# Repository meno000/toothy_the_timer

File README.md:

# toothy_the_timer
A little PCB project that helps kids brush teeth for the proper amount of time.

It uses the Atmet Attiny85 along with some shift registers and various LEDs, etc.

Schematics were created in KiCad. Gerbers are available if you'd like to send the board out to a fab house.

Note that this repository does not have a bootloader in it. You'll have to find/roll your own. This is mainly to avoid any issues with USB VID/PID numbers.

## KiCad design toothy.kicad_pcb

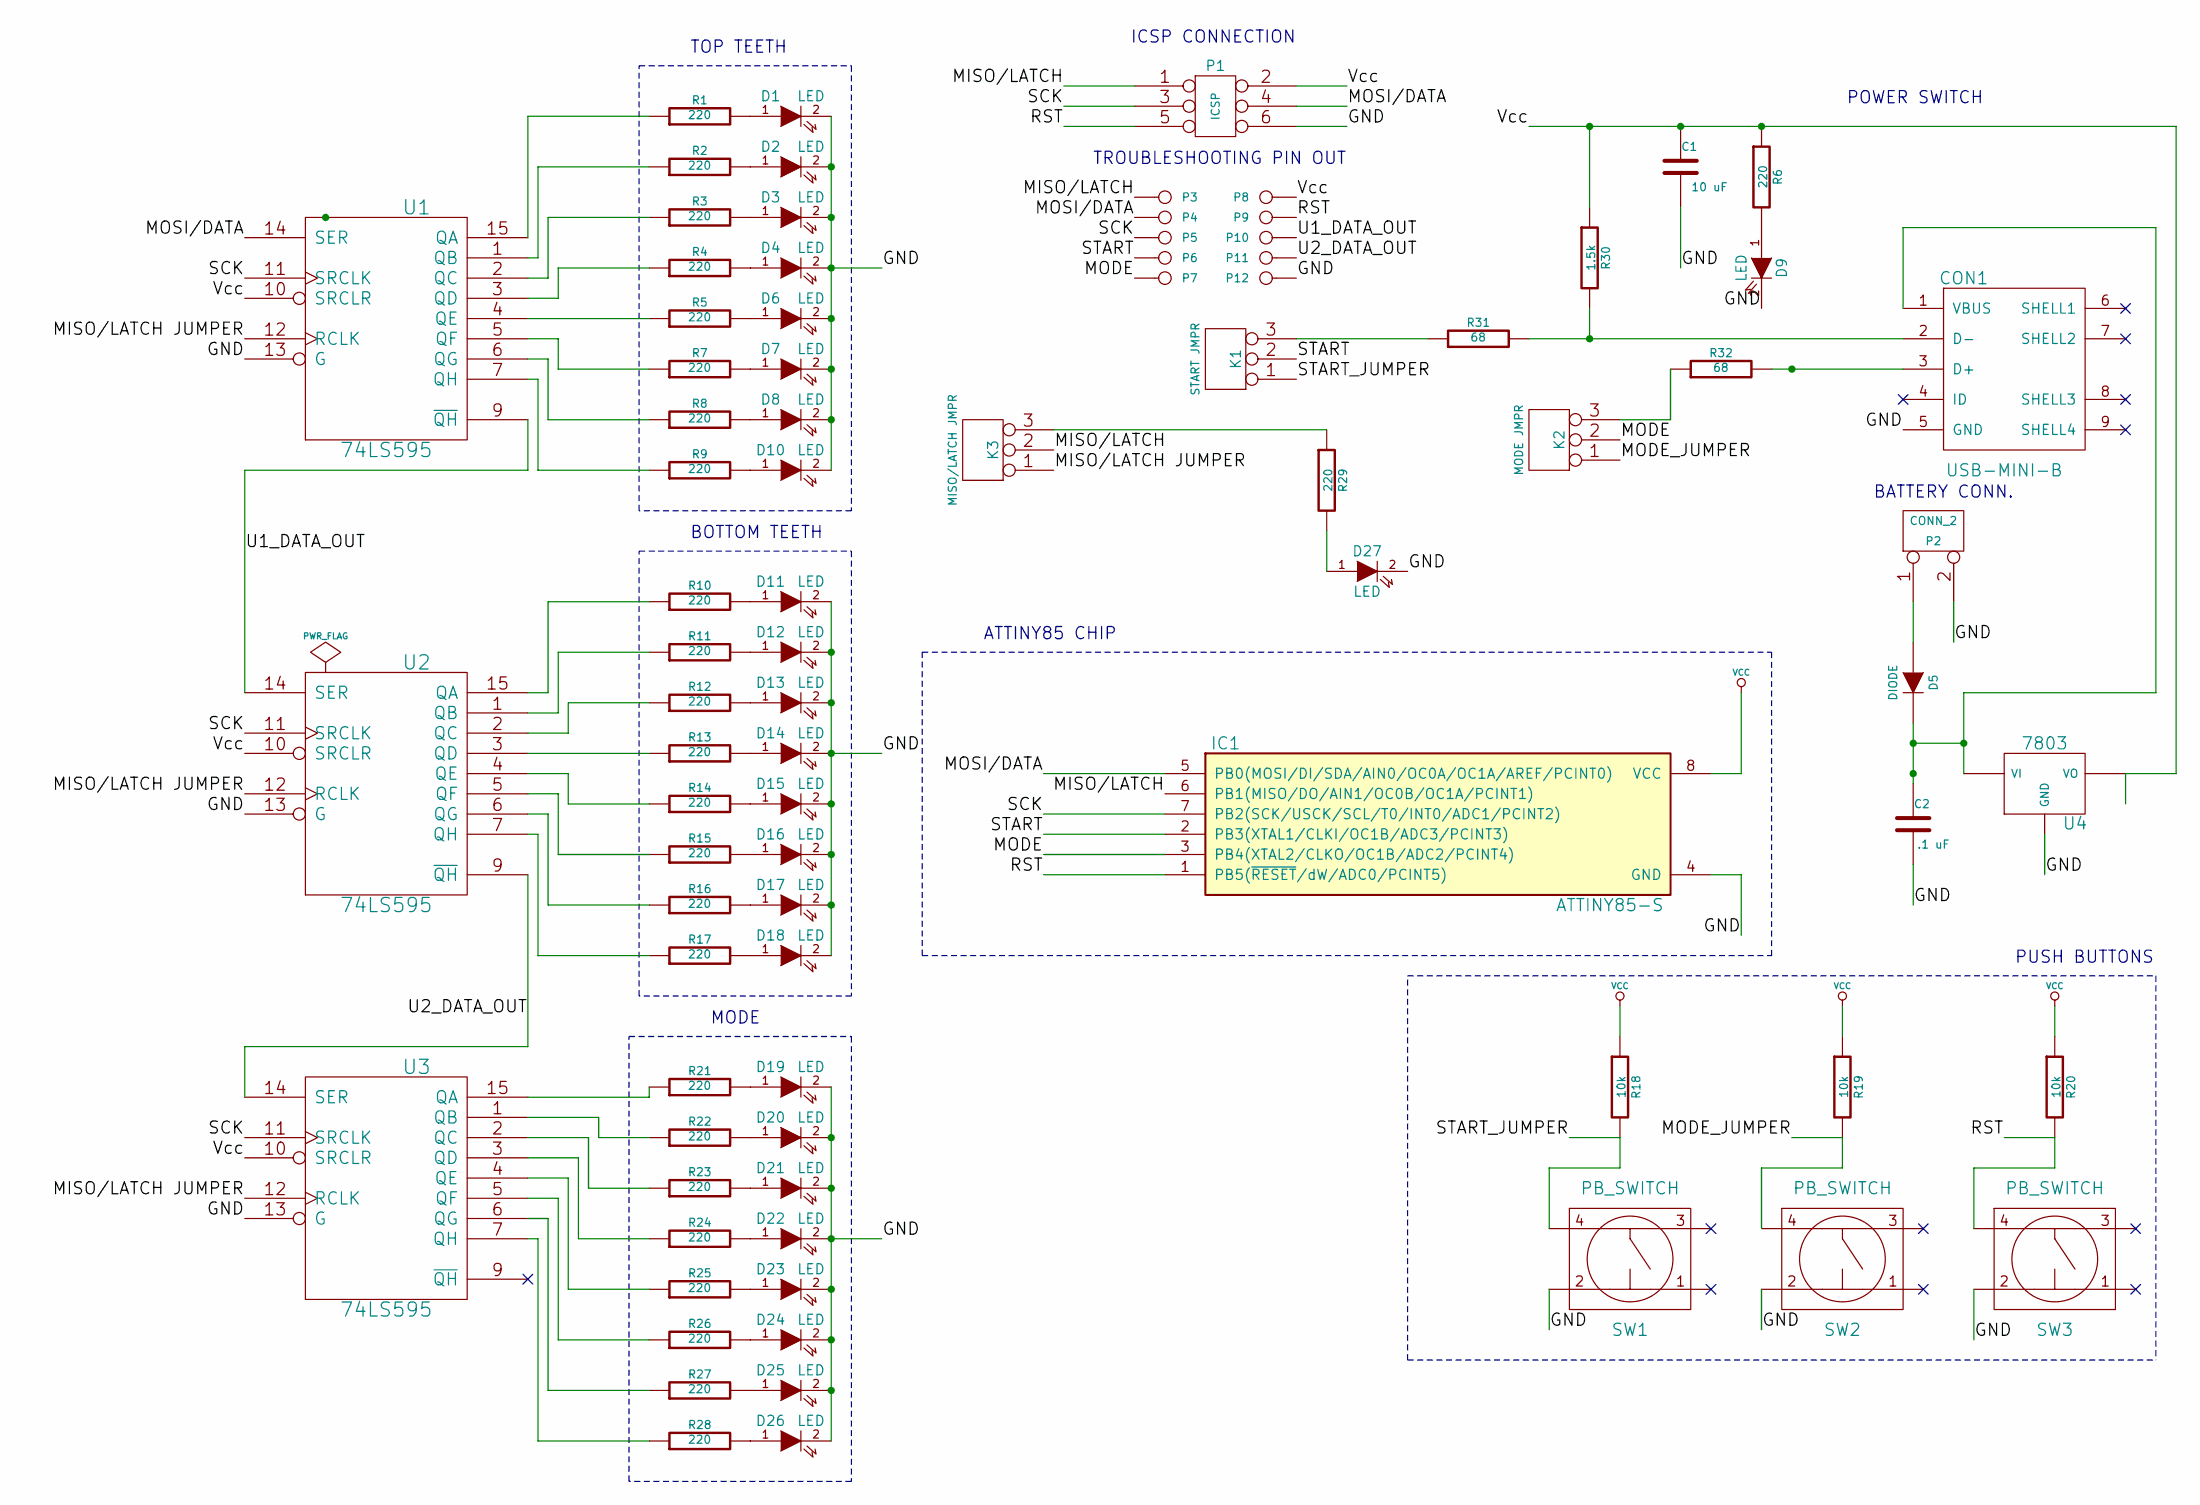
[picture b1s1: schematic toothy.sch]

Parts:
C1: 10 uF
C2: .1 uF
CON1: USB-MINI-B
D1, D2, D3, D4, D6, D7, D8, D9, D10, D11, D12, D13, D14, D15, D16, D17, D18, D19, D20, D21, D22, D23, D24, D25, D26, D27: LED
D5: DIODE
IC1: ATTINY85-S; SO8-200
K1: START JMPR
K2: MODE JMPR
K3: MISO/LATCH JMPR
P1: ICSP
P2: CONN_2
P3, P4, P5, P6, P7, P8, P9, P10, P11, P12: CONN_1
R1, R2, R3, R4, R5, R6, R7, R8, R9, R10, R11, R12, R13, R14, R15, R16, R17, R21, R22, R23, R24, R25, R26, R27, R28, R29: 220
R18, R19, R20: 10k
R30: 1.5k
R31, R32: 68
SW1, SW2, SW3: PB_SWITCH
U1, U2, U3: 74LS595
U4: 7803

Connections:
/MISO/LATCH: IC1.6 (PB1(MISO/DO/AIN1/OC0B/OC1A/PCINT1)), K3.2 (PM), P1.1, P3.1
/MISO/LATCH JUMPER: K3.1, U1.12 (RCLK), U2.12 (RCLK), U3.12 (RCLK)
/MODE: IC1.3 (PB4(XTAL2/CLKO/OC1B/ADC2/PCINT4)), K2.2 (PM), P7.1
/MODE_JUMPER: K2.1, R19.2, SW2.4
/MOSI/DATA: IC1.5 (PB0(MOSI/DI/SDA/AIN0/OC0A/OC1A/AREF/PCI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), P1.4, P4.1, U1.14 (SER)
/RST: IC1.1 (PB5(~RESET~/dW/ADC0/PCINT5)), P1.5, P9.1, R20.2, SW3.4
/SCK: IC1.7 (PB2(SCK/USCK/SCL/T0/INT0/ADC1/PCINT2)), P1.3, P5.1, U1.11 (SRCLK), U2.11 (SRCLK), U3.11 (SRCLK)
/START: IC1.2 (PB3(XTAL1/CLKI/OC1B/ADC3/PCINT3)), K1.2 (PM), P6.1
/START_JUMPER: K1.1, R18.2, SW1.4
/U1_DATA_OUT: P10.1, U1.9 (~QH), U2.14 (SER)
/U2_DATA_OUT: P11.1, U2.9 (~QH), U3.14 (SER)
GND: C1.2, C2.2, CON1.5 (GND), D1.2 (K), D2.2 (K), D3.2 (K), D4.2 (K), D6.2 (K), D7.2 (K), D8.2 (K), D9.2 (K), D10.2 (K), D11.2 (K), D12.2 (K), D13.2 (K), D14.2 (K), D15.2 (K), D16.2 (K), D17.2 (K), D18.2 (K), D19.2 (K), D20.2 (K), D21.2 (K), D22.2 (K), D23.2 (K), D24.2 (K), D25.2 (K), D26.2 (K), D27.2 (K), IC1.4 (GND), P1.6, P2.2 (PM), P12.1, SW1.2, SW2.2, SW3.2, U1.8 (GND), U1.13 (G), U2.8 (GND), U2.13 (G), U3.8 (GND), U3.13 (G), U4.GND
unnamed: D27.1 (A), R29.2
unnamed: CON1.2 (D-), R30.2, R31.2
unnamed: K2.3, R32.1
unnamed: D5.1 (A), P2.1
unnamed: K3.3, R29.1
unnamed: K1.3, R31.1
unnamed: R1.1, U1.15 (QA)
unnamed: R2.1, U1.1 (QB)
unnamed: R3.1, U1.2 (QC)
unnamed: R4.1, U1.3 (QD)
unnamed: C2.1, CON1.1 (VBUS), D5.2 (K), U4.VI
unnamed: CON1.3 (D+), R32.2
unnamed: R15.1, U2.5 (QF)
unnamed: R16.1, U2.6 (QG)
unnamed: R17.1, U2.7 (QH)
unnamed: R21.1, U3.15 (QA)
unnamed: R22.1, U3.1 (QB)
unnamed: R23.1, U3.2 (QC)
unnamed: R24.1, U3.3 (QD)
unnamed: R25.1, U3.4 (QE)
unnamed: R26.1, U3.5 (QF)
unnamed: R27.1, U3.6 (QG)
unnamed: R28.1, U3.7 (QH)
unnamed: R5.1, U1.4 (QE)
unnamed: R7.1, U1.5 (QF)
unnamed: R8.1, U1.6 (QG)
unnamed: R9.1, U1.7 (QH)
unnamed: R10.1, U2.15 (QA)
unnamed: R11.1, U2.1 (QB)
unnamed: R12.1, U2.2 (QC)
unnamed: R13.1, U2.3 (QD)
unnamed: R14.1, U2.4 (QE)
unnamed: D1.1 (A), R1.2
unnamed: D10.1 (A), R9.2
unnamed: D8.1 (A), R8.2
unnamed: D7.1 (A), R7.2
unnamed: D6.1 (A), R5.2
unnamed: D4.1 (A), R4.2
unnamed: D3.1 (A), R3.2
unnamed: D2.1 (A), R2.2
unnamed: D26.1 (A), R28.2
unnamed: D25.1 (A), R27.2
unnamed: D24.1 (A), R26.2
unnamed: D23.1 (A), R25.2
unnamed: D22.1 (A), R24.2
unnamed: D21.1 (A), R23.2
unnamed: D20.1 (A), R22.2
unnamed: D19.1 (A), R21.2
unnamed: D14.1 (A), R13.2
unnamed: D13.1 (A), R12.2
unnamed: D12.1 (A), R11.2
unnamed: D11.1 (A), R10.2
unnamed: D9.1 (A), R6.2
unnamed: D18.1 (A), R17.2
unnamed: D17.1 (A), R16.2
unnamed: D16.1 (A), R15.2
unnamed: D15.1 (A), R14.2
VCC: C1.1, IC1.8 (VCC), P1.2, P8.1, R6.1, R18.1, R19.1, R20.1, R30.1, U1.10 (SRCLR), U1.16 (VCC), U2.10 (SRCLR), U2.16 (VCC), U3.10 (SRCLR), U3.16 (VCC), U4.VO

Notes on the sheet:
TOP TEETH
BOTTOM TEETH
MODE
ATTINY85 CHIP
PUSH BUTTONS
ICSP CONNECTION
POWER SWITCH
BATTERY CONN.
TROUBLESHOOTING PIN OUT

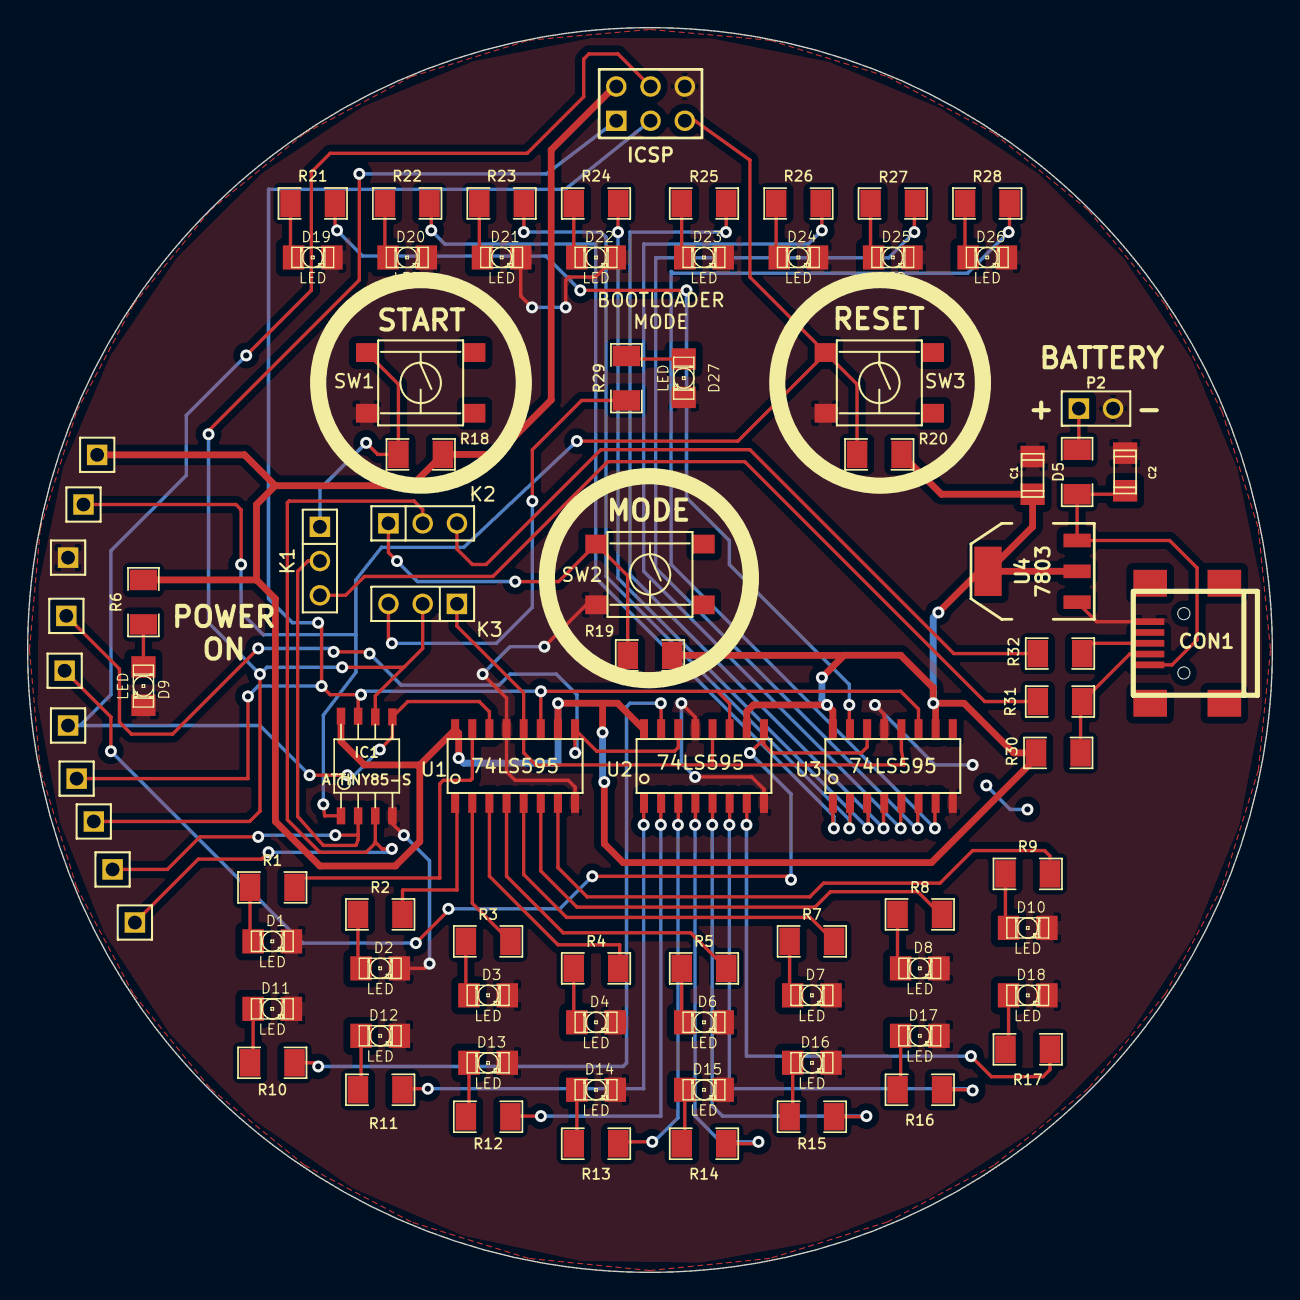
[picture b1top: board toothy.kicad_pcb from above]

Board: 2 copper layers, 92.3 x 92.3 mm, 85 parts (0 on the bottom side), 70 nets.

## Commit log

2015-05-14 minor updates
2015-05-15 Code and documentation updates
